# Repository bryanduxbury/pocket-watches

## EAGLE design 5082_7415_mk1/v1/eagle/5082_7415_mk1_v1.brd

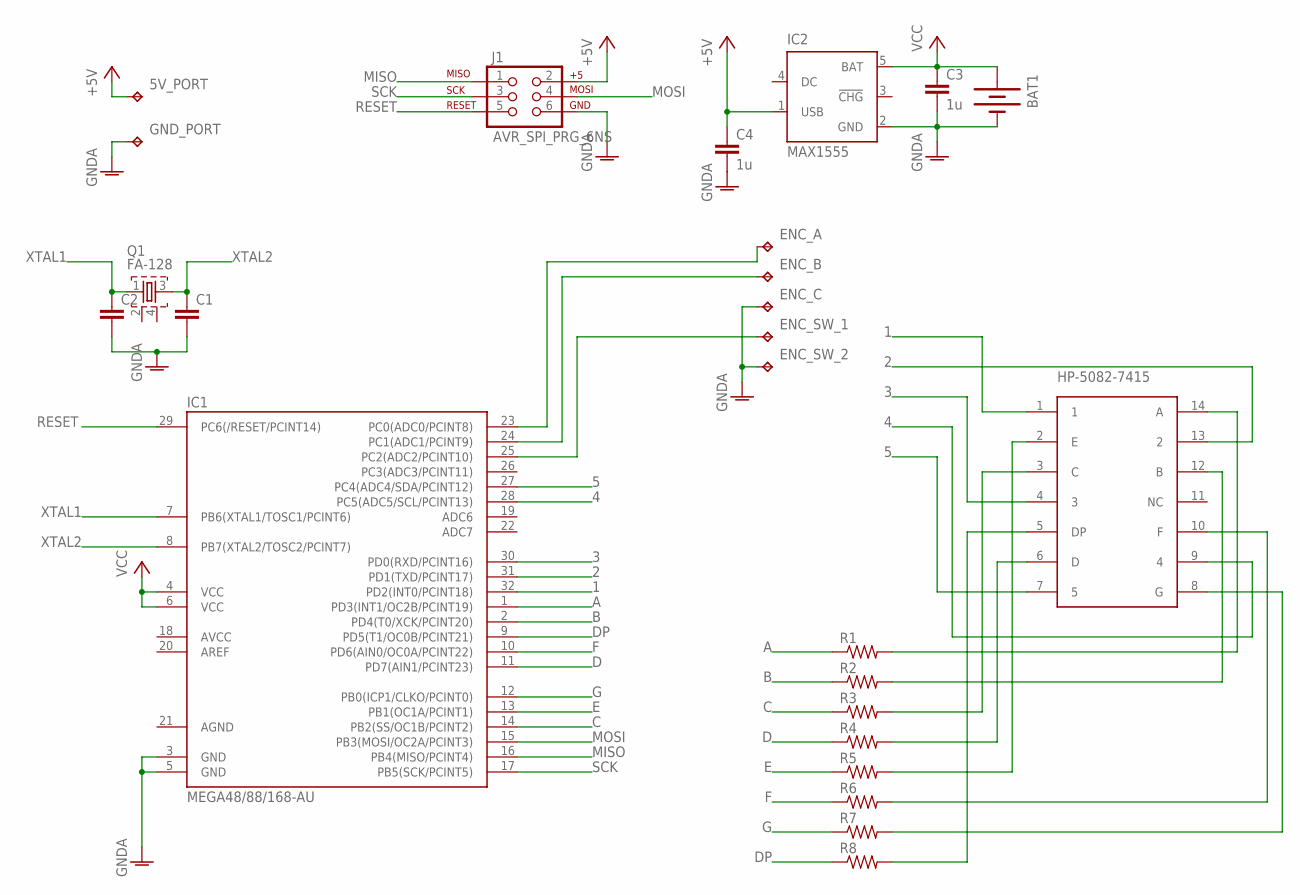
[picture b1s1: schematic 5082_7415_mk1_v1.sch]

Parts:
5V_PORT: TPB2,54; B2,54
BAT1: BATTERY245MM; BATTCON_245MM
C1, C2: C-EUC0805; C0805
C3, C4: 1u; C0805
ENC_A: TPTP20SQ; TP20SQ
ENC_B: TPTP20SQ; TP20SQ
ENC_C: TPTP20SQ; TP20SQ
ENC_SW_1, ENC_SW_2: TPTP20SQ; TP20SQ
GND_PORT: TPB2,54; B2,54
IC1: MEGA48/88/168-AU; TQFP32-08
IC2: MAX1555; SOT23-5L
J1: AVR_SPI_PRG_6NS; 2X3-NS
Q1: FA-128
R1, R2, R3, R4, R5, R6, R7, R8: R-US_M0805; M0805
U$1: HP-5082-7415; DIL14

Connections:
1: IC1.32 (PD2(INT0/PCINT18)), U$1.1
2: IC1.31 (PD1(TXD/PCINT17)), U$1.13 (2)
3: IC1.30 (PD0(RXD/PCINT16)), U$1.4 (3)
4: IC1.28 (PC5(ADC5/SCL/PCINT13)), U$1.9 (4)
5: IC1.27 (PC4(ADC4/SDA/PCINT12)), U$1.7 (5)
+5V: 5V_PORT.TP, C4.1, IC2.1 (USB), J1.2
A: IC1.1 (PD3(INT1/OC2B/PCINT19)), R1.1
AGND: IC1.21 (AGND)
B: IC1.2 (PD4(T0/XCK/PCINT20)), R2.1
C: IC1.14 (PB2(SS/OC1B/PCINT2)), R3.1
D: IC1.11 (PD7(AIN1/PCINT23)), R4.1
DP: IC1.9 (PD5(T1/OC0B/PCINT21)), R8.1
E: IC1.13 (PB1(OC1A/PCINT1)), R5.1
F: IC1.10 (PD6(AIN0/OC0A/PCINT22)), R6.1
G: IC1.12 (PB0(ICP1/CLKO/PCINT0)), R7.1
GNDA: BAT1.2 (-), C1.2, C2.2, C3.2, C4.2, ENC_C.TP, ENC_SW_2.TP, GND_PORT.TP, IC1.3 (GND), IC1.5 (GND), IC2.2 (GND), J1.6
MISO: IC1.16 (PB4(MISO/PCINT4)), J1.1
MOSI: IC1.15 (PB3(MOSI/OC2A/PCINT3)), J1.4
unnamed: R1.2, U$1.14 (A)
unnamed: R2.2, U$1.12 (B)
unnamed: R3.2, U$1.3 (C)
unnamed: R4.2, U$1.6 (D)
unnamed: R5.2, U$1.2 (E)
unnamed: R6.2, U$1.10 (F)
unnamed: R7.2, U$1.8 (G)
unnamed: R8.2, U$1.5 (DP)
unnamed: ENC_A.TP, IC1.23 (PC0(ADC0/PCINT8))
unnamed: ENC_B.TP, IC1.24 (PC1(ADC1/PCINT9))
unnamed: ENC_SW_1.TP, IC1.25 (PC2(ADC2/PCINT10))
RESET: IC1.29 (PC6(/RESET/PCINT14)), J1.5
SCK: IC1.17 (PB5(SCK/PCINT5)), J1.3
VCC: BAT1.1 (+), C3.1, IC1.4 (VCC), IC1.6 (VCC), IC2.5 (BAT)
XTAL1: C2.1, IC1.7 (PB6(XTAL1/TOSC1/PCINT6)), Q1.1
XTAL2: C1.1, IC1.8 (PB7(XTAL2/TOSC2/PCINT7)), Q1.3

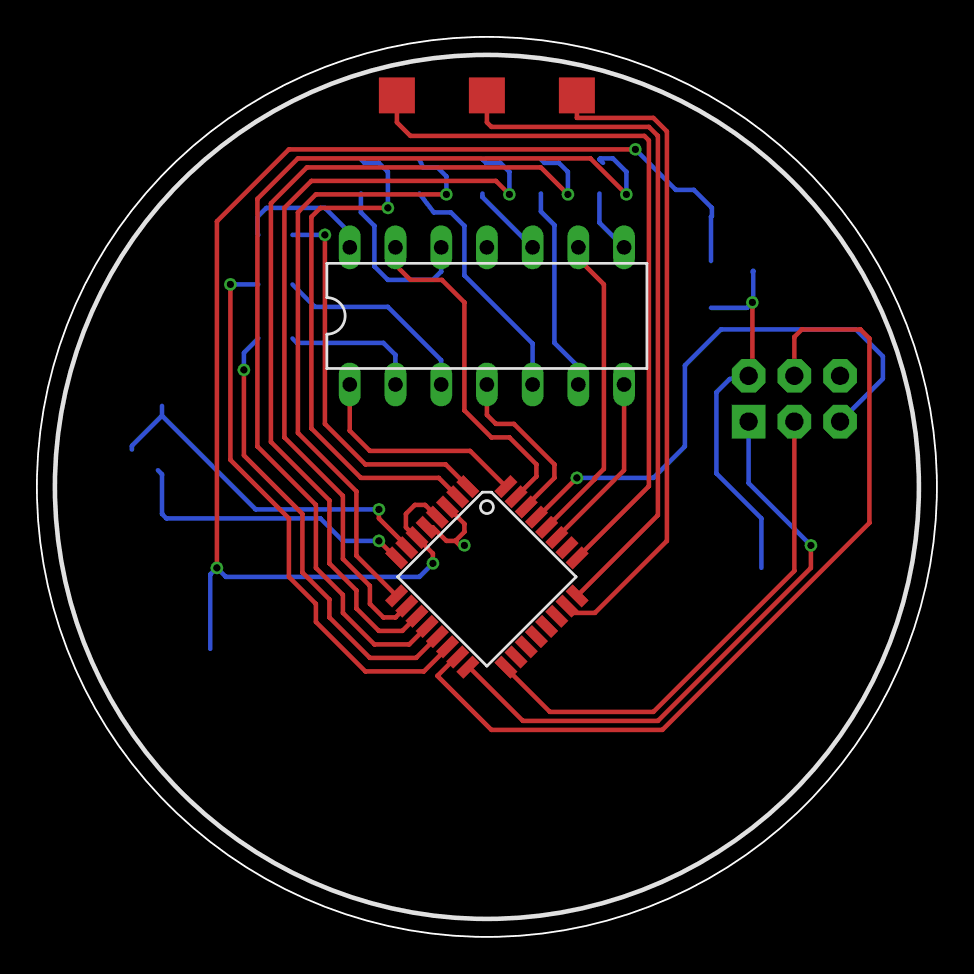
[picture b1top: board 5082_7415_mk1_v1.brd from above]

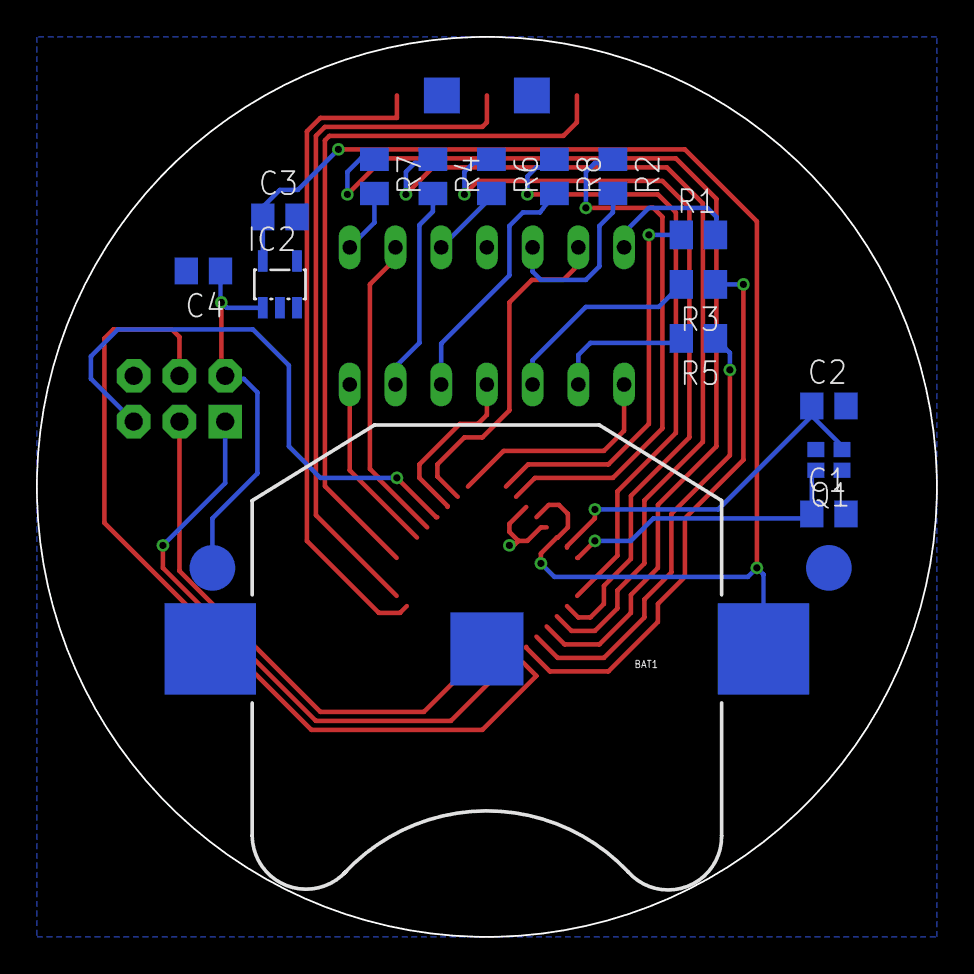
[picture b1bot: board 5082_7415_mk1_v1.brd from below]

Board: 2 copper layers, 50.0 x 50.0 mm, 25 parts (19 on the bottom side), 33 nets.

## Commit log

2015-08-13 init commit

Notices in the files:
parts and their libraries:
SparkFun-Connectors: Licensing: Creative Commons ShareAlike 4.0 International - https://creativecommons.org/licenses/by-sa/4.0
